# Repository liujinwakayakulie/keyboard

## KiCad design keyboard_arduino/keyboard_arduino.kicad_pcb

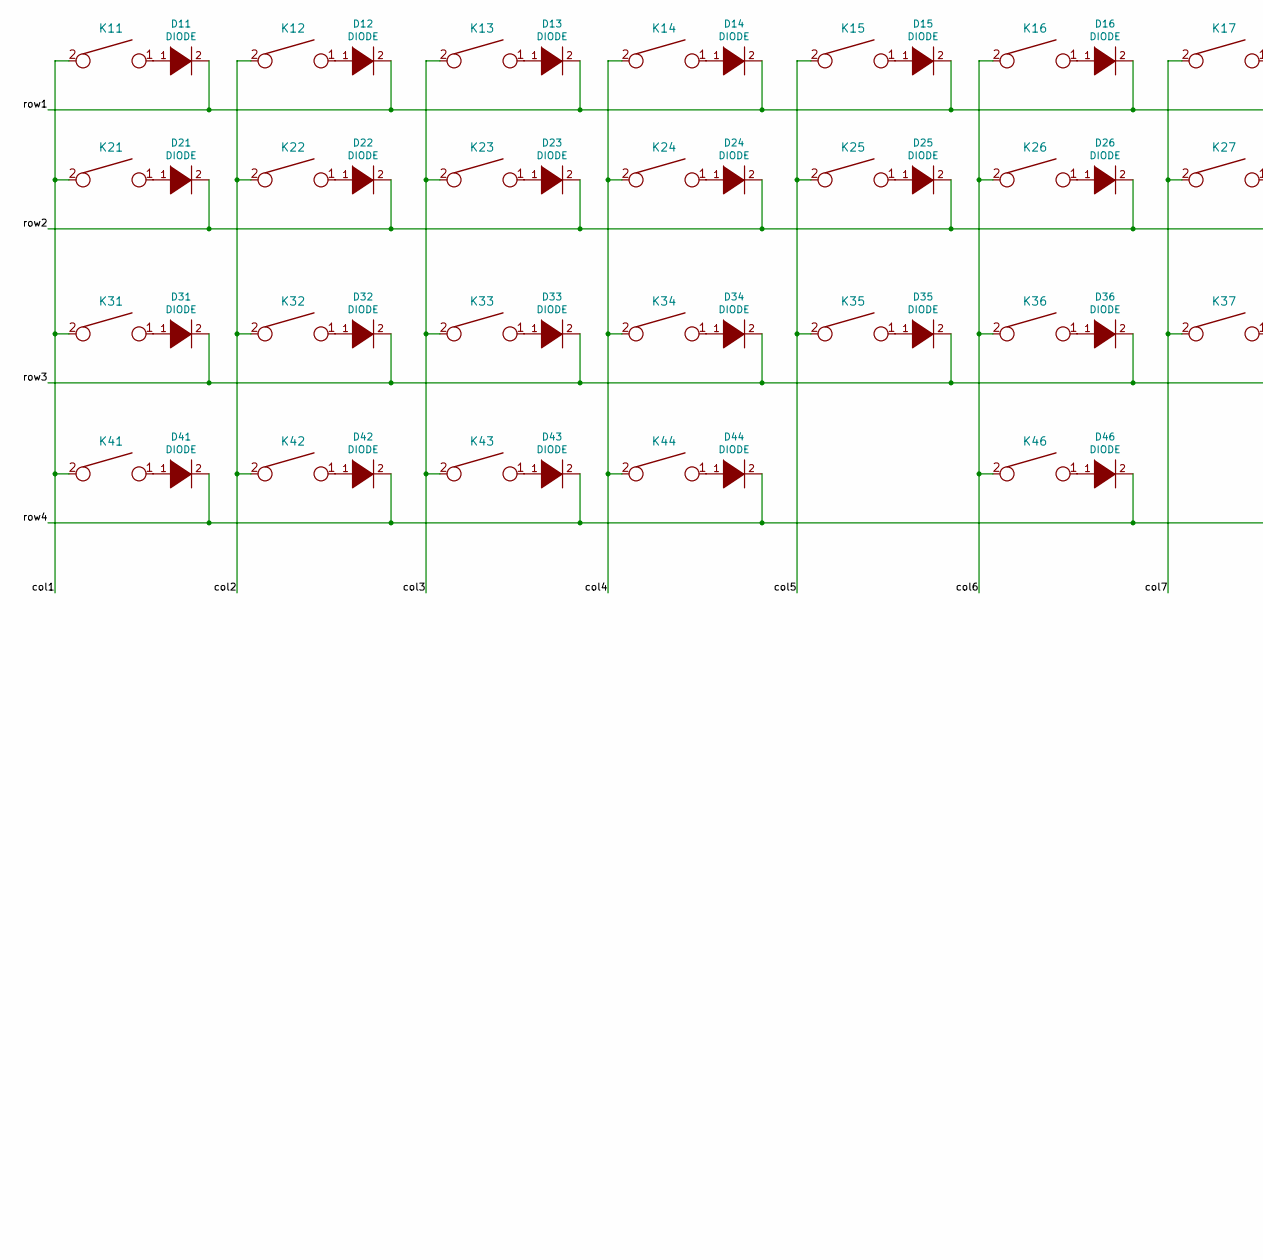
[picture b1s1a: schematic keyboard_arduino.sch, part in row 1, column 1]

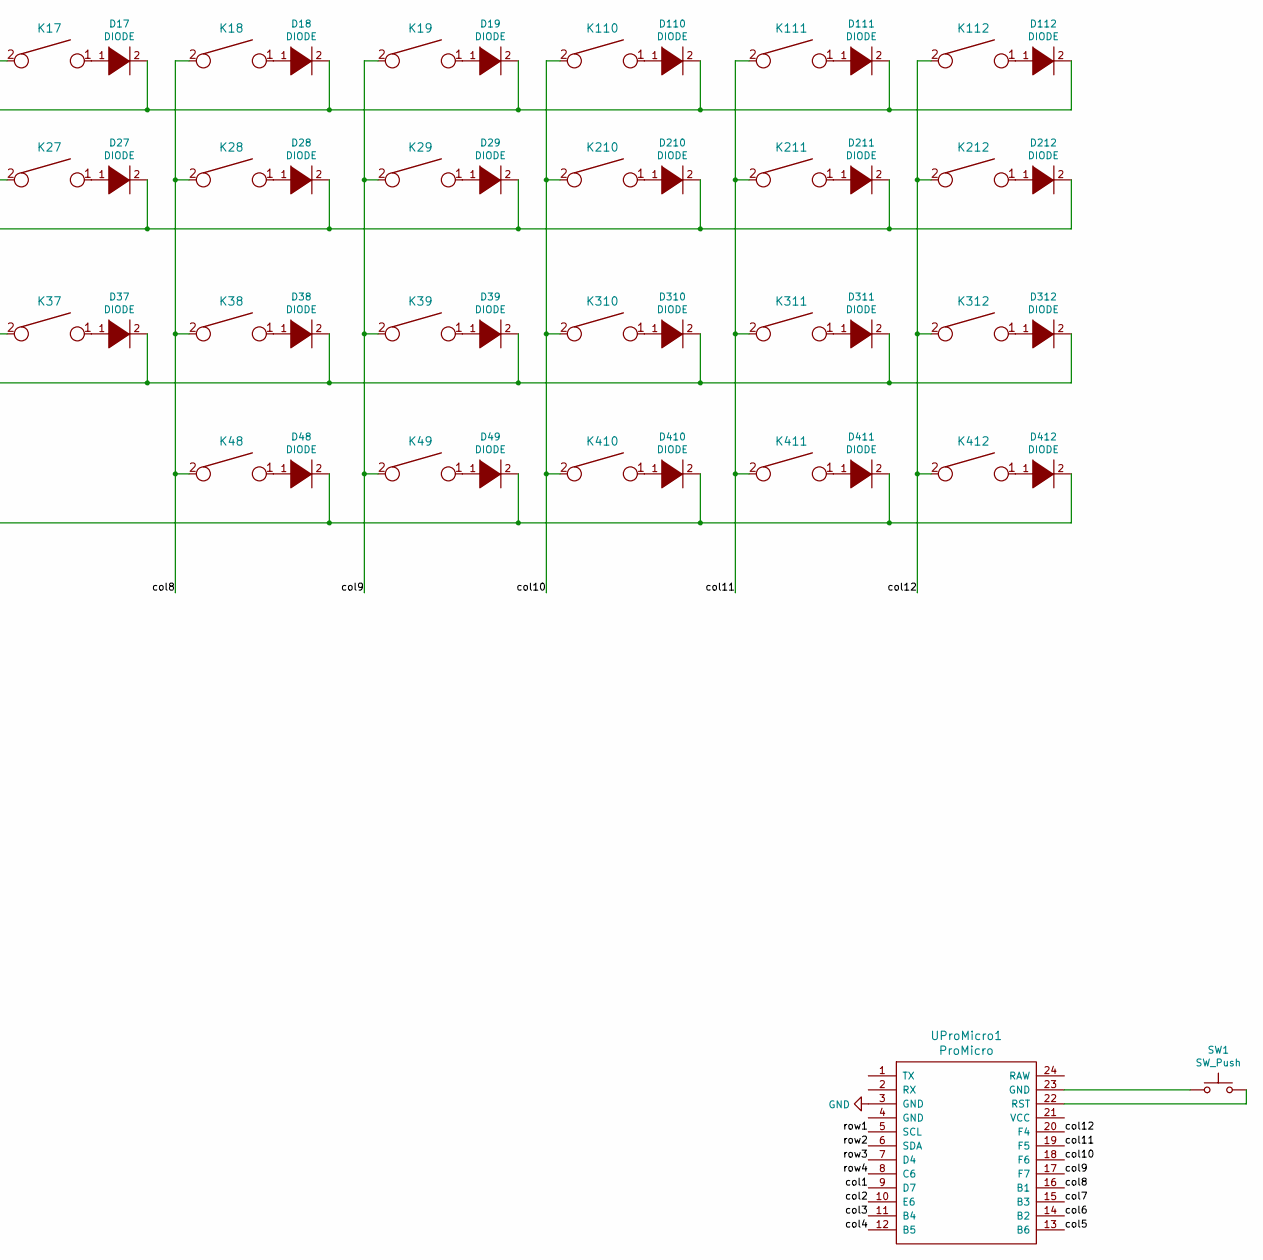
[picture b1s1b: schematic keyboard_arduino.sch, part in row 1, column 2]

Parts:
D11, D12, D13, D14, D15, D16, D17, D18, D19, D21, D22, D23, D24, D25, D26, D27, D28, D29, D31, D32, D33, D34, D35, D36, D37, D38, D39, D41, D42, D43, D44, D46, D48, D49, D110, D111, D112, D210, D211, D212, D310, D311, D312, D410, D411, D412: DIODE; D_1206_3216Metric
K11, K12, K13, K14, K15, K16, K17, K18, K19, K21, K22, K23, K24, K25, K26, K27, K28, K29, K31, K32, K33, K34, K35, K36, K37, K38, K39, K41, K42, K43, K44, K49, K110, K111, K112, K210, K211, K212, K310, K311, K312, K410, K411, K412: KEYSW; CHERRY_PCB_100H
K46: KEYSW; CHERRY_PCB_275H
K48: KEYSW; CHERRY_PCB_125H
SW1: SW_Push; SW_SPST_CK_RS282G05A3
UProMicro1: ProMicro

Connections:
/col1: K11.2, K21.2, K31.2, K41.2, UProMicro1.9 (D7)
/col2: K12.2, K22.2, K32.2, K42.2, UProMicro1.10 (E6)
/col3: K13.2, K23.2, K33.2, K43.2, UProMicro1.11 (B4)
/col4: K14.2, K24.2, K34.2, K44.2, UProMicro1.12 (B5)
/col5: K15.2, K25.2, K35.2, UProMicro1.13 (B6)
/col6: K16.2, K26.2, K36.2, K46.2, UProMicro1.14 (B2)
/col7: K17.2, K27.2, K37.2, UProMicro1.15 (B3)
/col8: K18.2, K28.2, K38.2, K48.2, UProMicro1.16 (B1)
/col9: K19.2, K29.2, K39.2, K49.2, UProMicro1.17 (F7)
/col10: K110.2, K210.2, K310.2, K410.2, UProMicro1.18 (F6)
/col11: K111.2, K211.2, K311.2, K411.2, UProMicro1.19 (F5)
/col12: K112.2, K212.2, K312.2, K412.2, UProMicro1.20 (F4)
/row1: D11.2 (A), D12.2 (A), D13.2 (A), D14.2 (A), D15.2 (A), D16.2 (A), D17.2 (A), D18.2 (A), D19.2 (A), D110.2 (A), D111.2 (A), D112.2 (A), UProMicro1.5 (SCL)
/row2: D21.2 (A), D22.2 (A), D23.2 (A), D24.2 (A), D25.2 (A), D26.2 (A), D27.2 (A), D28.2 (A), D29.2 (A), D210.2 (A), D211.2 (A), D212.2 (A), UProMicro1.6 (SDA)
/row3: D31.2 (A), D32.2 (A), D33.2 (A), D34.2 (A), D35.2 (A), D36.2 (A), D37.2 (A), D38.2 (A), D39.2 (A), D310.2 (A), D311.2 (A), D312.2 (A), UProMicro1.7 (D4)
/row4: D41.2 (A), D42.2 (A), D43.2 (A), D44.2 (A), D46.2 (A), D48.2 (A), D49.2 (A), D410.2 (A), D411.2 (A), D412.2 (A), UProMicro1.8 (C6)
GND: UProMicro1.3 (GND)
unnamed: D11.1 (K), K11.1
unnamed: D12.1 (K), K12.1
unnamed: D13.1 (K), K13.1
unnamed: D14.1 (K), K14.1
unnamed: D15.1 (K), K15.1
unnamed: D16.1 (K), K16.1
unnamed: D17.1 (K), K17.1
unnamed: D18.1 (K), K18.1
unnamed: D19.1 (K), K19.1
unnamed: D21.1 (K), K21.1
unnamed: D22.1 (K), K22.1
unnamed: D23.1 (K), K23.1
unnamed: D24.1 (K), K24.1
unnamed: D25.1 (K), K25.1
unnamed: D26.1 (K), K26.1
unnamed: D27.1 (K), K27.1
unnamed: D28.1 (K), K28.1
unnamed: D29.1 (K), K29.1
unnamed: D31.1 (K), K31.1
unnamed: D32.1 (K), K32.1
unnamed: D33.1 (K), K33.1
unnamed: D34.1 (K), K34.1
unnamed: D35.1 (K), K35.1
unnamed: D36.1 (K), K36.1
unnamed: D37.1 (K), K37.1
unnamed: D38.1 (K), K38.1
unnamed: D39.1 (K), K39.1
unnamed: D41.1 (K), K41.1
unnamed: D42.1 (K), K42.1
unnamed: D43.1 (K), K43.1
unnamed: D44.1 (K), K44.1
unnamed: D46.1 (K), K46.1
unnamed: D48.1 (K), K48.1
unnamed: D49.1 (K), K49.1
unnamed: D110.1 (K), K110.1
unnamed: D111.1 (K), K111.1
unnamed: D112.1 (K), K112.1
unnamed: D210.1 (K), K210.1
unnamed: D211.1 (K), K211.1
unnamed: D212.1 (K), K212.1
unnamed: D310.1 (K), K310.1
unnamed: D311.1 (K), K311.1
unnamed: D312.1 (K), K312.1
unnamed: D410.1 (K), K410.1
unnamed: D411.1 (K), K411.1
unnamed: D412.1 (K), K412.1
unnamed: SW1.1, UProMicro1.23 (GND)
unnamed: SW1.2, UProMicro1.22 (RST)

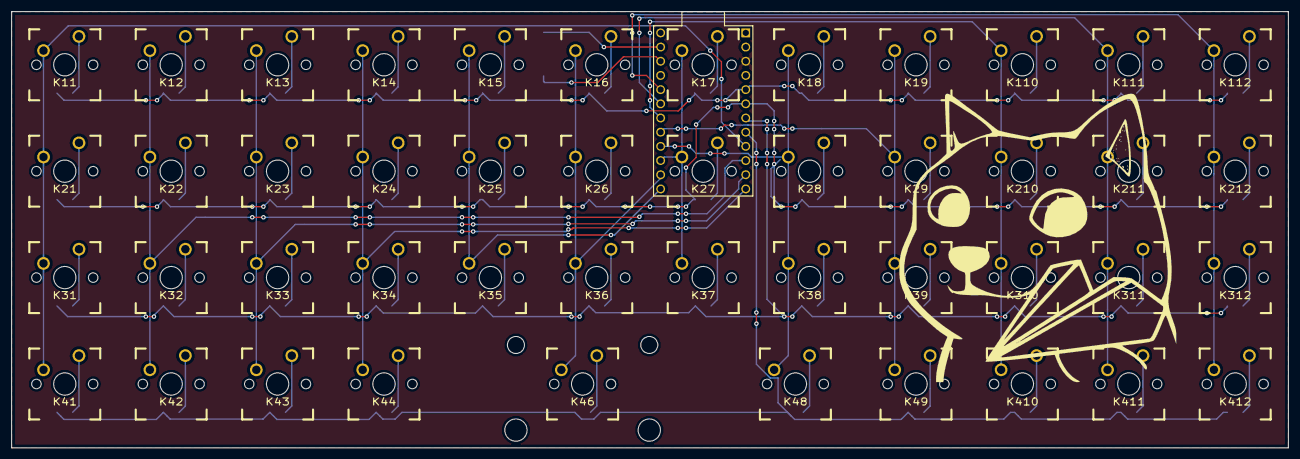
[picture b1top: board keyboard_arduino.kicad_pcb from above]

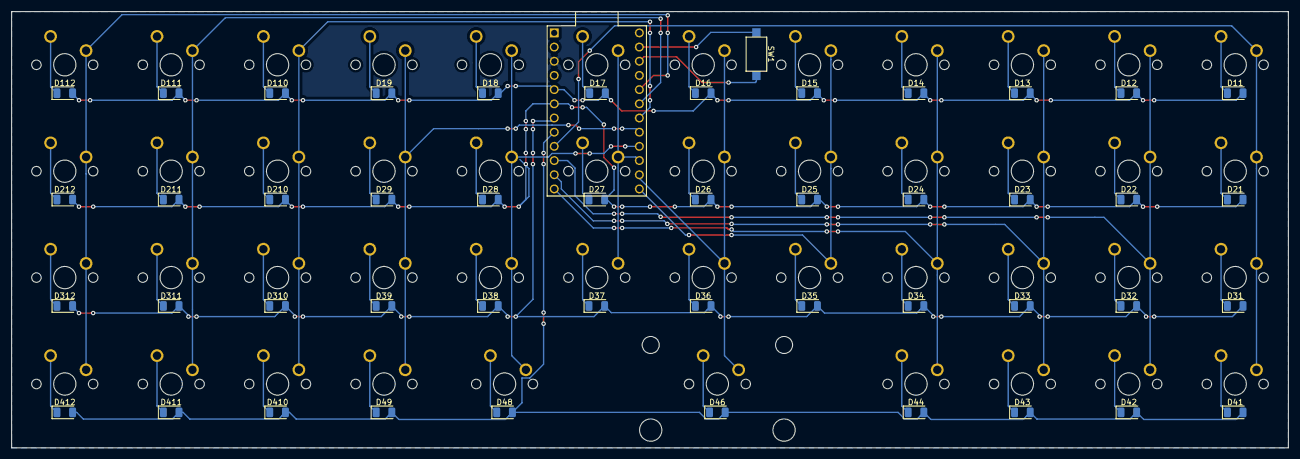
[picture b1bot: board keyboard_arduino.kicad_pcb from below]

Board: 2 copper layers, 228.6 x 78.1 mm, 94 parts (48 on the bottom side), 64 nets.

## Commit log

2019-04-27 first commit includ pcb and cad
